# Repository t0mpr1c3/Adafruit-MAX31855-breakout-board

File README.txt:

Adafruit MAX31885 Thermocouple Amp breakout

These are the Eagle CAD files for the Adafruit MAX31885 Thermocouple Amp breakout:
  ----> http://www.adafruit.com/products/269

Adafruit invests time and resources providing this open source design, please support Adafruit and open-source hardware by purchasing products from Adafruit!

Thermocouples are very sensitive, requiring a good amplifier with a cold-compensation reference. The MAX31855K does everything for you, and can be easily interfaced with any microcontroller, even one without an analog input. This breakout board has the chip itself, a 3.3V regulator with 10uF bypass capacitors and level shifting circuitry, all assembled and tested. Comes with a 2 pin terminal block (for connecting to the thermocouple) and pin header (to plug into any breadboard or perfboard). Goes great with our 1m K-type thermocouple. 

All text above must be included in any redistribution

Designed by Limor Fried/Ladyada for Adafruit Industries.
Creative Commons Attribution/Share-Alike, all text above must be included in any redistribution

Modified Tom Price 16 Sep 2013

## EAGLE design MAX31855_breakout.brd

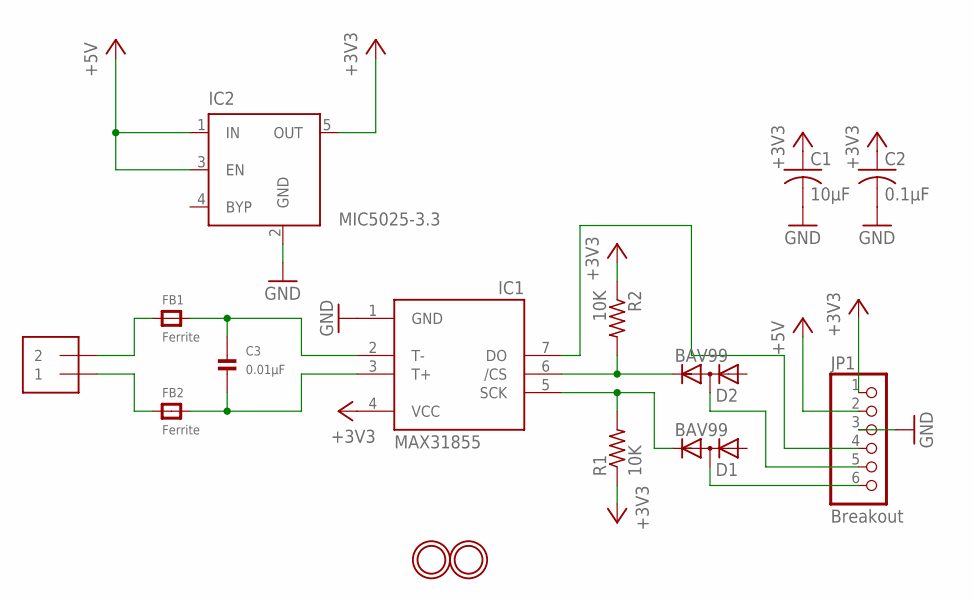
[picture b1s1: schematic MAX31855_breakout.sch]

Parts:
C1: 10µF; C0805K
C2: 0.1µF; C0805K
C3: 0.01µF; _0805
D1, D2: BAV99; SOT23
FB1, FB2: Ferrite; _0805
IC1: MAX31855; SO08
IC2: MIC5025-3.3; SOT23-5
J1: 1X2-3.5MM
JP1: Breakout; 1X06_ROUND_76
R1, R2: 10K; R0805
U$4, U$5: MOUNTINGHOLE2.0; MOUNTINGHOLE_2.0_PLATED

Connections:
+3V3: C1.1, C2.1, IC1.4 (VCC), IC2.5 (OUT), JP1.1, R1.1, R2.1
+5V: IC2.1 (IN), IC2.3 (EN), JP1.2
DO: IC1.7 (DO), JP1.4
GND: C1.2, C2.2, IC1.1 (GND), IC2.2 (GND), JP1.3
unnamed: FB1.1, J1.2
unnamed: D2.3 (AC), JP1.5
unnamed: D1.3 (AC), JP1.6
unnamed: C3.1, FB1.2, IC1.2 (T-)
unnamed: FB2.1, J1.1
unnamed: C3.2, FB2.2, IC1.3 (T+)
unnamed: D2.2 (C), IC1.6 (/CS), R2.2
SCK: D1.2 (C), IC1.5 (SCK), R1.2

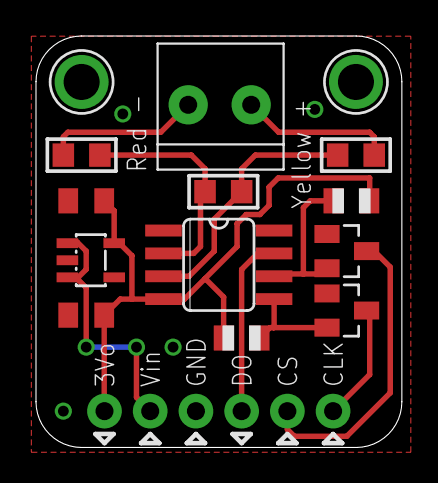
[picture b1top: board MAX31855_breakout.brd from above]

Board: 2 copper layers, 20.3 x 22.9 mm, 15 parts (0 on the bottom side), 12 nets.

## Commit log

2013-10-06 modifications to Adafruit MAX31855 breakout v2 for OSHpark
